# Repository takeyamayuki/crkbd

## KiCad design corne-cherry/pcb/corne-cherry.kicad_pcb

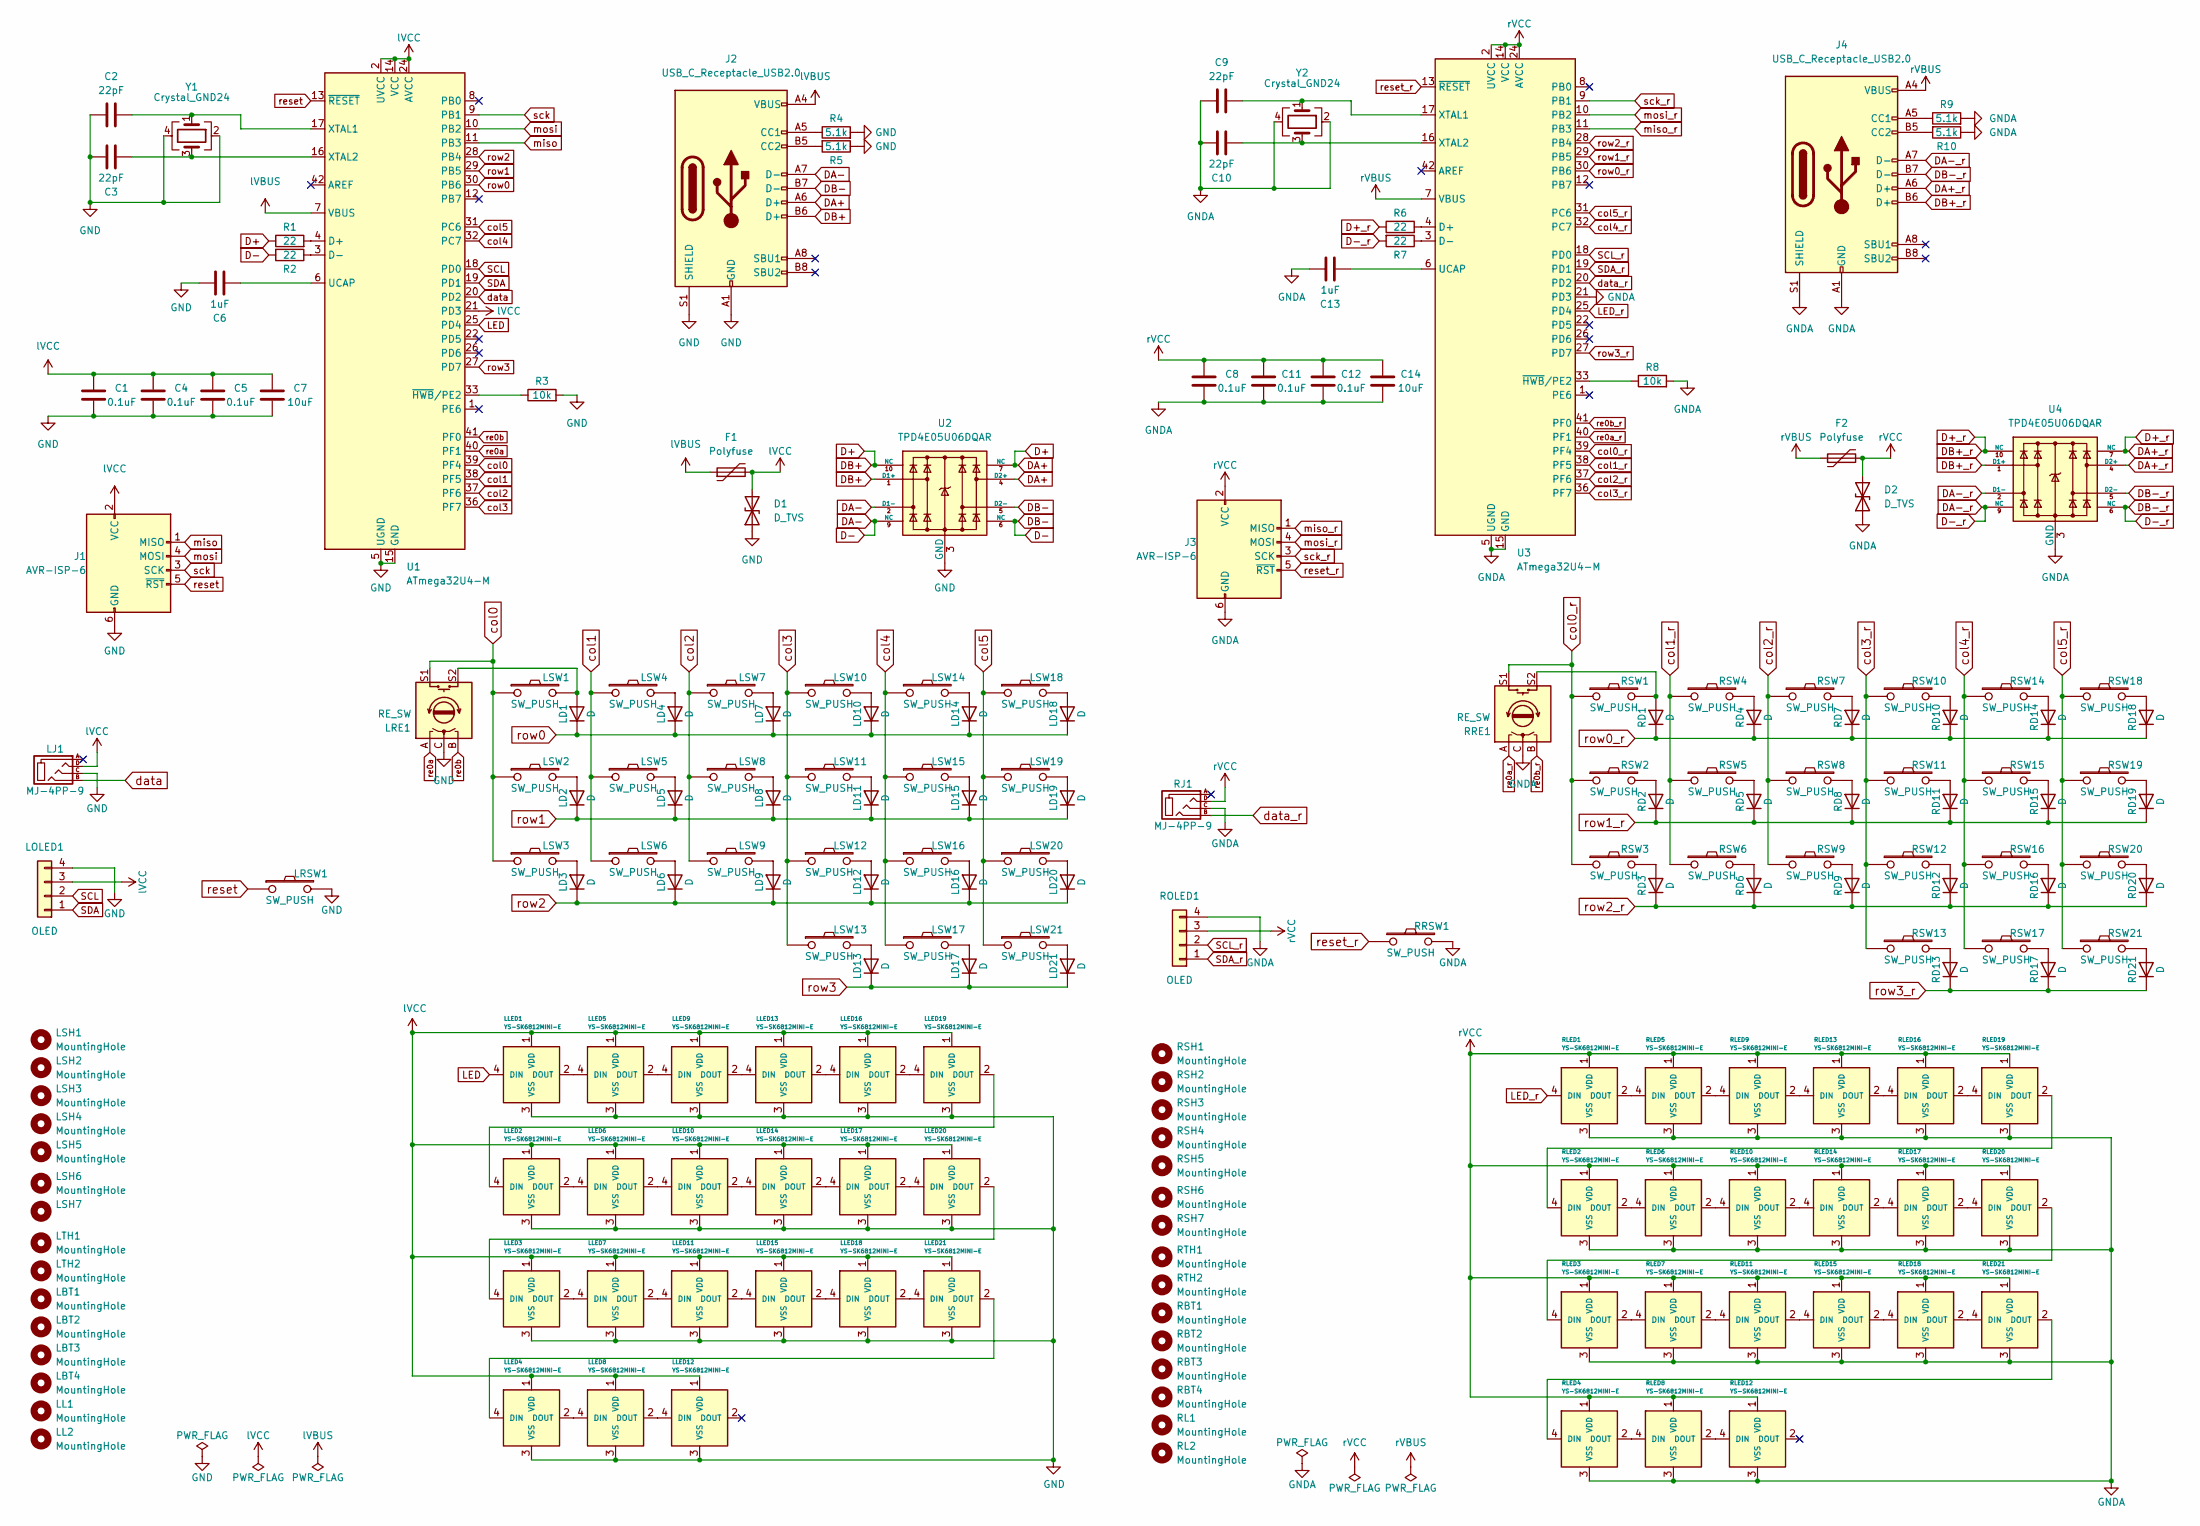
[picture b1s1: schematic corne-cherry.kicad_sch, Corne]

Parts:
C1, C4, C5, C8, C11, C12: 0.1uF; C_0603_1608Metric
C2, C3, C9, C10: 22pF; C_0603_1608Metric
C6, C13: 1uF; C_0603_1608Metric
C7, C14: 10uF; C_0603_1608Metric
D1, D2: D_TVS; D_SOD-123
F1, F2: Polyfuse; Fuse_1206_3216Metric
J1, J3: AVR-ISP-6
J2, J4: USB_C_Receptacle_USB2.0; USB_C_Receptacle_HRO_TYPE-C-31-M-12
LBT1, LBT2, LBT3, LBT4: MountingHole; Breakaway_Tabs
LD1, LD2, LD3, LD4, LD5, LD6, LD7, LD8, LD9, LD10, LD11, LD12, LD13, LD14, LD15, LD16, LD17, LD18, LD19, LD20, LD21: D; D3_SMD_v2
LJ1: MJ-4PP-9; MJ-4PP-9_1side
LL1, LL2: MountingHole; corne-logo-horizontal
LLED1, LLED2, LLED3, LLED4, LLED5, LLED6, LLED7, LLED8, LLED9, LLED10, LLED11, LLED12, LLED13, LLED14, LLED15, LLED16, LLED17, LLED18, LLED19, LLED20, LLED21: YS-SK6812MINI-E
LOLED1: OLED; OLED_1side
LRE1: RE_SW; RotaryEncoder_EC12-SW
LRSW1: SW_PUSH; ResetSW
LSH1, LSH2, LSH3, LSH4, LSH5, LSH6: MountingHole; spacer_m2
LSH7: (no value)
LSW1, LSW2, LSW3, LSW4, LSW5, LSW6, LSW7, LSW8, LSW9, LSW10, LSW11, LSW12, LSW13, LSW14, LSW15, LSW16, LSW17, LSW18, LSW19, LSW20: SW_PUSH; CherryMX_Hotswap
LSW21: SW_PUSH; CherryMX_Hotswap_1.5u
LTH1, LTH2: MountingHole; thread_m2
R1, R2, R6, R7: 22; R_0603_1608Metric
R3, R8: 10k; R_0603_1608Metric
R4, R5, R9, R10: 5.1k; R_0603_1608Metric
RBT1, RBT2, RBT3, RBT4: MountingHole; Breakaway_Tabs
RD1, RD2, RD3, RD4, RD5, RD6, RD7, RD8, RD9, RD10, RD11, RD12, RD13, RD14, RD15, RD16, RD17, RD18, RD19, RD20, RD21: D; D3_SMD_v2
RJ1: MJ-4PP-9; MJ-4PP-9_1side
RL1, RL2: MountingHole; corne-logo-horizontal
RLED1, RLED2, RLED3, RLED4, RLED5, RLED6, RLED7, RLED8, RLED9, RLED10, RLED11, RLED12, RLED13, RLED14, RLED15, RLED16, RLED17, RLED18, RLED19, RLED20, RLED21: YS-SK6812MINI-E
ROLED1: OLED; OLED_1side
RRE1: RE_SW; RotaryEncoder_EC12-SW
RRSW1: SW_PUSH; ResetSW
RSH1, RSH2, RSH3, RSH4, RSH5, RSH6, RSH7: MountingHole; spacer_m2
RSW1, RSW2, RSW3, RSW4, RSW5, RSW6, RSW7, RSW8, RSW9, RSW10, RSW11, RSW12, RSW13, RSW14, RSW15, RSW16, RSW17, RSW18, RSW19, RSW20: SW_PUSH; CherryMX_Hotswap
RSW21: SW_PUSH; CherryMX_Hotswap_1.5u
RTH1, RTH2: MountingHole; thread_m2
U1, U3: ATmega32U4-M; QFN-44-1EP_7x7mm_P0.5mm_EP5.2x5.2mm
U2, U4: TPD4E05U06DQAR; USON-10_2.5x1.0mm_P0.5mm
Y1, Y2: Crystal_GND24; Crystal_SMD_3225-4Pin_3.2x2.5mm

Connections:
D+: J2.A6 (D+), J2.B6 (D+), R1.1, U2.1 (D1+), U2.4 (D2+), U2.7 (NC), U2.10 (NC)
D+_r: J4.A6 (D+), J4.B6 (D+), R6.1, U4.1 (D1+), U4.4 (D2+), U4.7 (NC), U4.10 (NC)
D-: J2.A7 (D-), J2.B7 (D-), R2.2, U2.2 (D1-), U2.5 (D2-), U2.6 (NC), U2.9 (NC)
D-_r: J4.A7 (D-), J4.B7 (D-), R7.2, U4.2 (D1-), U4.5 (D2-), U4.6 (NC), U4.9 (NC)
GND: C1.1, C2.1, C3.1, C4.1, C5.1, C6.1, C7.1, D1.1 (A1), J1.6 (GND), J2.A1 (GND), J2.A12 (GND), J2.B1 (GND), J2.B12 (GND), J2.S1 (SHIELD), LJ1.C, LLED1.3 (VSS), LLED2.3 (VSS), LLED3.3 (VSS), LLED4.3 (VSS), LLED5.3 (VSS), LLED6.3 (VSS), LLED7.3 (VSS), LLED8.3 (VSS), LLED9.3 (VSS), LLED10.3 (VSS), LLED11.3 (VSS), LLED12.3 (VSS), LLED13.3 (VSS), LLED14.3 (VSS), LLED15.3 (VSS), LLED16.3 (VSS), LLED17.3 (VSS), LLED18.3 (VSS), LLED19.3 (VSS), LLED20.3 (VSS), LLED21.3 (VSS), LOLED1.4, LRE1.C, LRSW1.2, R3.2, R4.2, R5.1, U1.5 (UGND), U1.15 (GND), U1.23 (GND), U1.35 (GND), U1.43 (GND), U1.45 (GND), U2.3 (GND), U2.8 (GND), Y1.2, Y1.4
GNDA: C8.1, C9.1, C10.1, C11.1, C12.1, C13.1, C14.1, D2.1 (A1), J3.6 (GND), J4.A1 (GND), J4.A12 (GND), J4.B1 (GND), J4.B12 (GND), J4.S1 (SHIELD), R8.2, R9.2, R10.1, RJ1.C, RLED1.3 (VSS), RLED2.3 (VSS), RLED3.3 (VSS), RLED4.3 (VSS), RLED5.3 (VSS), RLED6.3 (VSS), RLED7.3 (VSS), RLED8.3 (VSS), RLED9.3 (VSS), RLED10.3 (VSS), RLED11.3 (VSS), RLED12.3 (VSS), RLED13.3 (VSS), RLED14.3 (VSS), RLED15.3 (VSS), RLED16.3 (VSS), RLED17.3 (VSS), RLED18.3 (VSS), RLED19.3 (VSS), RLED20.3 (VSS), RLED21.3 (VSS), ROLED1.4, RRE1.C, RRSW1.2, U3.5 (UGND), U3.15 (GND), U3.21 (PD3), U3.23 (GND), U3.35 (GND), U3.43 (GND), U3.45 (GND), U4.3 (GND), U4.8 (GND), Y2.2, Y2.4
LED: LLED1.4 (DIN), U1.25 (PD4)
LED_r: RLED1.4 (DIN), U3.25 (PD4)
unnamed: C2.2, U1.17 (XTAL1), Y1.1
unnamed: C3.2, U1.16 (XTAL2), Y1.3
unnamed: C6.2, U1.6 (UCAP)
unnamed: C9.2, U3.17 (XTAL1), Y2.1
unnamed: C10.2, U3.16 (XTAL2), Y2.3
unnamed: C13.2, U3.6 (UCAP)
unnamed: J2.A5 (CC1), R4.1
unnamed: J2.B5 (CC2), R5.2
unnamed: J4.A5 (CC1), R9.1
unnamed: J4.B5 (CC2), R10.2
unnamed: LD1.2 (A), LRE1.S2, LSW1.2
unnamed: LD2.2 (A), LSW2.2
unnamed: LD3.2 (A), LSW3.2
unnamed: LD4.2 (A), LSW4.2
unnamed: LD5.2 (A), LSW5.2
unnamed: LD6.2 (A), LSW6.2
unnamed: LD7.2 (A), LSW7.2
unnamed: LD8.2 (A), LSW8.2
unnamed: LD9.2 (A), LSW9.2
unnamed: LD10.2 (A), LSW10.2
unnamed: LD11.2 (A), LSW11.2
unnamed: LD12.2 (A), LSW12.2
unnamed: LD13.2 (A), LSW13.2
unnamed: LD14.2 (A), LSW14.2
unnamed: LD15.2 (A), LSW15.2
unnamed: LD16.2 (A), LSW16.2
unnamed: LD17.2 (A), LSW17.2
unnamed: LD18.2 (A), LSW18.2
unnamed: LD19.2 (A), LSW19.2
unnamed: LD20.2 (A), LSW20.2
unnamed: LD21.2 (A), LSW21.2
unnamed: LLED1.2 (DOUT), LLED5.4 (DIN)
unnamed: LLED2.2 (DOUT), LLED6.4 (DIN)
unnamed: LLED3.2 (DOUT), LLED7.4 (DIN)
unnamed: LLED4.2 (DOUT), LLED8.4 (DIN)
unnamed: LLED5.2 (DOUT), LLED9.4 (DIN)
unnamed: LLED10.2 (DOUT), LLED14.4 (DIN)
unnamed: LLED6.2 (DOUT), LLED10.4 (DIN)
unnamed: LLED11.2 (DOUT), LLED15.4 (DIN)
unnamed: LLED7.2 (DOUT), LLED11.4 (DIN)
unnamed: LLED8.2 (DOUT), LLED12.4 (DIN)
unnamed: LLED13.2 (DOUT), LLED16.4 (DIN)
unnamed: LLED9.2 (DOUT), LLED13.4 (DIN)
unnamed: LLED14.2 (DOUT), LLED17.4 (DIN)
unnamed: LLED15.2 (DOUT), LLED18.4 (DIN)
unnamed: LLED16.2 (DOUT), LLED19.4 (DIN)
unnamed: LLED17.2 (DOUT), LLED20.4 (DIN)
unnamed: LLED18.2 (DOUT), LLED21.4 (DIN)
unnamed: LLED2.4 (DIN), LLED19.2 (DOUT)
unnamed: LLED3.4 (DIN), LLED20.2 (DOUT)
unnamed: LLED4.4 (DIN), LLED21.2 (DOUT)
unnamed: R1.2, U1.4 (D+)
unnamed: R2.1, U1.3 (D-)
unnamed: R3.1, U1.33 (~HWB/PE2)
unnamed: R6.2, U3.4 (D+)
unnamed: R7.1, U3.3 (D-)
unnamed: R8.1, U3.33 (~HWB/PE2)
unnamed: RD1.2 (A), RRE1.S2, RSW1.2
unnamed: RD2.2 (A), RSW2.2
unnamed: RD3.2 (A), RSW3.2
unnamed: RD4.2 (A), RSW4.2
unnamed: RD5.2 (A), RSW5.2
unnamed: RD6.2 (A), RSW6.2
unnamed: RD7.2 (A), RSW7.2
unnamed: RD8.2 (A), RSW8.2
unnamed: RD9.2 (A), RSW9.2
unnamed: RD10.2 (A), RSW10.2
unnamed: RD11.2 (A), RSW11.2
unnamed: RD12.2 (A), RSW12.2
unnamed: RD13.2 (A), RSW13.2
unnamed: RD14.2 (A), RSW14.2
unnamed: RD15.2 (A), RSW15.2
unnamed: RD16.2 (A), RSW16.2
unnamed: RD17.2 (A), RSW17.2
unnamed: RD18.2 (A), RSW18.2
unnamed: RD19.2 (A), RSW19.2
unnamed: RD20.2 (A), RSW20.2
unnamed: RD21.2 (A), RSW21.2
unnamed: RLED1.2 (DOUT), RLED5.4 (DIN)
unnamed: RLED2.2 (DOUT), RLED6.4 (DIN)
unnamed: RLED3.2 (DOUT), RLED7.4 (DIN)
unnamed: RLED4.2 (DOUT), RLED8.4 (DIN)
unnamed: RLED5.2 (DOUT), RLED9.4 (DIN)
unnamed: RLED10.2 (DOUT), RLED14.4 (DIN)
unnamed: RLED6.2 (DOUT), RLED10.4 (DIN)
unnamed: RLED11.2 (DOUT), RLED15.4 (DIN)
unnamed: RLED7.2 (DOUT), RLED11.4 (DIN)
unnamed: RLED8.2 (DOUT), RLED12.4 (DIN)
unnamed: RLED13.2 (DOUT), RLED16.4 (DIN)
unnamed: RLED9.2 (DOUT), RLED13.4 (DIN)
unnamed: RLED14.2 (DOUT), RLED17.4 (DIN)
unnamed: RLED15.2 (DOUT), RLED18.4 (DIN)
unnamed: RLED16.2 (DOUT), RLED19.4 (DIN)
unnamed: RLED17.2 (DOUT), RLED20.4 (DIN)
unnamed: RLED18.2 (DOUT), RLED21.4 (DIN)
unnamed: RLED2.4 (DIN), RLED19.2 (DOUT)
unnamed: RLED3.4 (DIN), RLED20.2 (DOUT)
unnamed: RLED4.4 (DIN), RLED21.2 (DOUT)
SCL: LOLED1.2, U1.18 (PD0)
SCL_r: ROLED1.2, U3.18 (PD0)
SDA: LOLED1.1, U1.19 (PD1)
SDA_r: ROLED1.1, U3.19 (PD1)
col0: LRE1.S1, LSW1.1, LSW2.1, LSW3.1, U1.39 (PF4)
col0_r: RRE1.S1, RSW1.1, RSW2.1, RSW3.1, U3.39 (PF4)
col1: LSW4.1, LSW5.1, LSW6.1, U1.38 (PF5)
col1_r: RSW4.1, RSW5.1, RSW6.1, U3.38 (PF5)
col2: LSW7.1, LSW8.1, LSW9.1, U1.37 (PF6)
col2_r: RSW7.1, RSW8.1, RSW9.1, U3.37 (PF6)
col3: LSW10.1, LSW11.1, LSW12.1, LSW13.1, U1.36 (PF7)
col3_r: RSW10.1, RSW11.1, RSW12.1, RSW13.1, U3.36 (PF7)
col4: LSW14.1, LSW15.1, LSW16.1, LSW17.1, U1.32 (PC7)
col4_r: RSW14.1, RSW15.1, RSW16.1, RSW17.1, U3.32 (PC7)
col5: LSW18.1, LSW19.1, LSW20.1, LSW21.1, U1.31 (PC6)
col5_r: RSW18.1, RSW19.1, RSW20.1, RSW21.1, U3.31 (PC6)
data: LJ1.B, U1.20 (PD2)
data_r: RJ1.B, U3.20 (PD2)
lVBUS: F1.1, J2.A4 (VBUS), J2.A9 (VBUS), J2.B4 (VBUS), J2.B9 (VBUS), U1.7 (VBUS)
lVCC: C1.2, C4.2, C5.2, C7.2, D1.2 (A2), F1.2, J1.2 (VCC), LJ1.D, LLED1.1 (VDD), LLED2.1 (VDD), LLED3.1 (VDD), LLED4.1 (VDD), LLED5.1 (VDD), LLED6.1 (VDD), LLED7.1 (VDD), LLED8.1 (VDD), LLED9.1 (VDD), LLED10.1 (VDD), LLED11.1 (VDD), LLED12.1 (VDD), LLED13.1 (VDD), LLED14.1 (VDD), LLED15.1 (VDD), LLED16.1 (VDD), LLED17.1 (VDD), LLED18.1 (VDD), LLED19.1 (VDD), LLED20.1 (VDD), LLED21.1 (VDD), LOLED1.3, U1.2 (UVCC), U1.14 (VCC), U1.21 (PD3), U1.24 (AVCC), U1.34 (VCC), U1.44 (AVCC)
miso: J1.1 (MISO), U1.11 (PB3)
miso_r: J3.1 (MISO), U3.11 (PB3)
mosi: J1.4 (MOSI), U1.10 (PB2)
mosi_r: J3.4 (MOSI), U3.10 (PB2)
rVBUS: F2.1, J4.A4 (VBUS), J4.A9 (VBUS), J4.B4 (VBUS), J4.B9 (VBUS), U3.7 (VBUS)
rVCC: C8.2, C11.2, C12.2, C14.2, D2.2 (A2), F2.2, J3.2 (VCC), RJ1.D, RLED1.1 (VDD), RLED2.1 (VDD), RLED3.1 (VDD), RLED4.1 (VDD), RLED5.1 (VDD), RLED6.1 (VDD), RLED7.1 (VDD), RLED8.1 (VDD), RLED9.1 (VDD), RLED10.1 (VDD), RLED11.1 (VDD), RLED12.1 (VDD), RLED13.1 (VDD), RLED14.1 (VDD), RLED15.1 (VDD), RLED16.1 (VDD), RLED17.1 (VDD), RLED18.1 (VDD), RLED19.1 (VDD), RLED20.1 (VDD), RLED21.1 (VDD), ROLED1.3, U3.2 (UVCC), U3.14 (VCC), U3.24 (AVCC), U3.34 (VCC), U3.44 (AVCC)
re0a: LRE1.A, U1.40 (PF1)
re0a_r: RRE1.A, U3.40 (PF1)
re0b: LRE1.B, U1.41 (PF0)
re0b_r: RRE1.B, U3.41 (PF0)
reset: J1.5 (~RST), LRSW1.1, U1.13 (~RESET)
reset_r: J3.5 (~RST), RRSW1.1, U3.13 (~RESET)
row0: LD1.1 (K), LD4.1 (K), LD7.1 (K), LD10.1 (K), LD14.1 (K), LD18.1 (K), U1.30 (PB6)
row0_r: RD1.1 (K), RD4.1 (K), RD7.1 (K), RD10.1 (K), RD14.1 (K), RD18.1 (K), U3.30 (PB6)
row1: LD2.1 (K), LD5.1 (K), LD8.1 (K), LD11.1 (K), LD15.1 (K), LD19.1 (K), U1.29 (PB5)
row1_r: RD2.1 (K), RD5.1 (K), RD8.1 (K), RD11.1 (K), RD15.1 (K), RD19.1 (K), U3.29 (PB5)
row2: LD3.1 (K), LD6.1 (K), LD9.1 (K), LD12.1 (K), LD16.1 (K), LD20.1 (K), U1.28 (PB4)
row2_r: RD3.1 (K), RD6.1 (K), RD9.1 (K), RD12.1 (K), RD16.1 (K), RD20.1 (K), U3.28 (PB4)
row3: LD13.1 (K), LD17.1 (K), LD21.1 (K), U1.27 (PD7)
row3_r: RD13.1 (K), RD17.1 (K), RD21.1 (K), U3.27 (PD7)
sck: J1.3 (SCK), U1.9 (PB1)
sck_r: J3.3 (SCK), U3.9 (PB1)

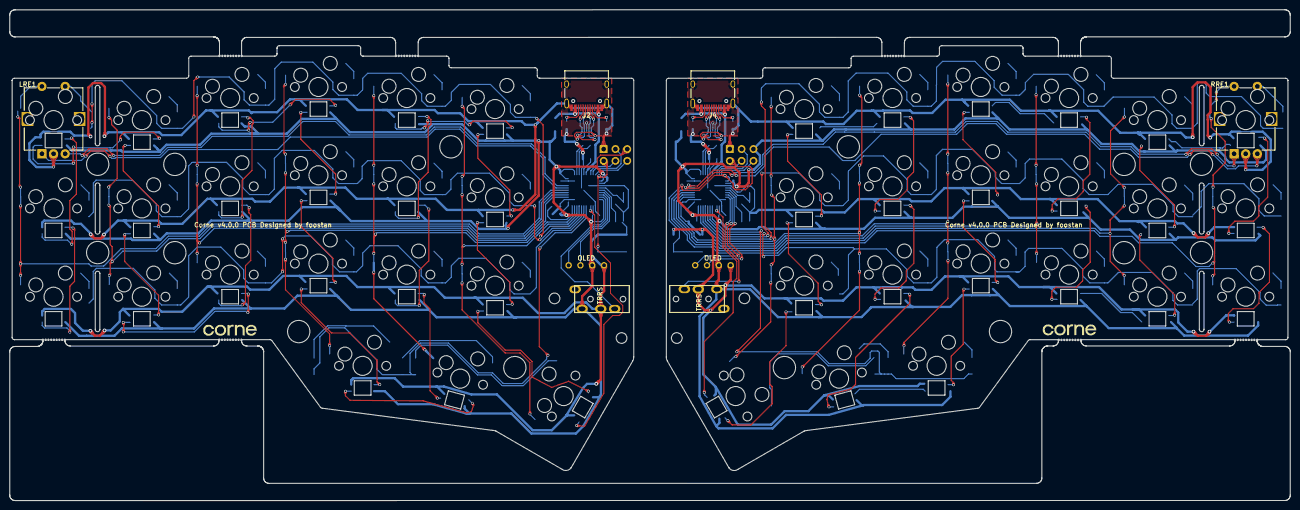
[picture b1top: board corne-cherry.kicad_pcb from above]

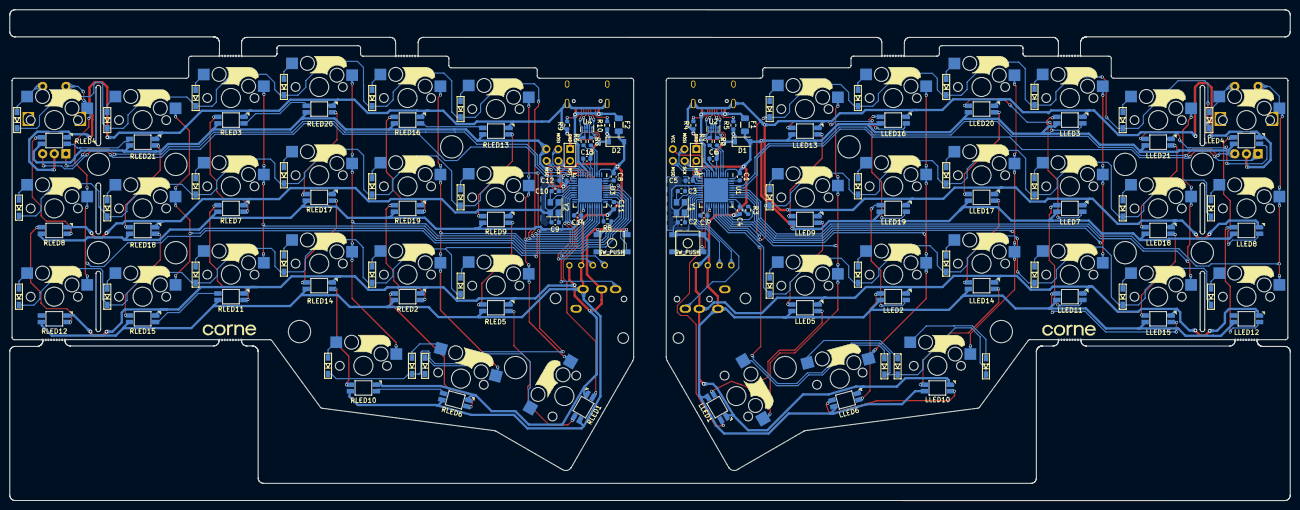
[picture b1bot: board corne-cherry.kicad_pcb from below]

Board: 2 copper layers, 275.5 x 105.6 mm, 202 parts (124 on the bottom side), 146 nets.

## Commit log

2021-12-26 Add the doc for corne-light-v2
2022-05-05 Update for v4
2023-07-21 add elecrow dxf
2023-07-28 add 100mm * 100mm
2023-07-30 add ver3
